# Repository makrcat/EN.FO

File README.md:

## outdoorsy-gadget

The **EN.FO** is a personal project for tracking the environment when outdoors. It measures altitude (pressure), temperature, humidity, and air quality through the BME680 chip. And it also has games now :3c

Around the end stages submitted to hack club stardance.

## Why I made this

I found a BME680 in a store, and I'd seen people making these home weather station setups and using temperature sensors for their first projects. I thought it would be cool to be able to track the weather while outside too, like while hiking or going somewhere without wifi! 

It would be pretty neat to get momentary values from a sensor for the surrounding area instead of looking online.

## CAD models

https://cad.onshape.com/documents/2de4779b51845175f3a3e786/w/7837df9d32ef23797361ec83/e/9a8511381228d62ac6592067?renderMode=0&uiState=6abf75e68beab4dd691114fb 

## Flashing to ESP32

**Materials:** 
- You want an esp32 with at least 512kb of RAM, or else it can't run the heavy graphics of circuitpython.
- You need a similar ST7789-driven screen, a microcontroller as specified above, and a bme680.
- Also, having a fuse would probably be good (just in case you short out components).

Install circuitpython! Then,

I use vscode to program, but I used Thonny to handle the flashing.
- Programs that go into the microcontroller are  `src`, `graphics`, `settings.json`, `logger.json`, and `fontsPCF`, side by side on root`/`. 
- You also have to install the libraries separately on Thonny, but it only takes a bit.

## In case you want to actually make one

Check if you are soldering the ESP-32 so that it's "bottom side up", or label-side up. The USB-C should be on the bottom. Same goes with the UPS module, make sure the USB-C is on the bottom. Or else you have to edit the CAD to match.

## Testing the program locally

I wanted to test the UI quickly, so the computer simulation is for that. The data is simulated in `mockIC.py`. 

`⚠️` Important note!! Open the `firmware` folder by itself! Otherwise, vscode will read the file paths incorrectly.

## Other images

This project originally started with a BMP & an e-ink, but gradually didn't work for the use case. I have a cool e-ink now, though.

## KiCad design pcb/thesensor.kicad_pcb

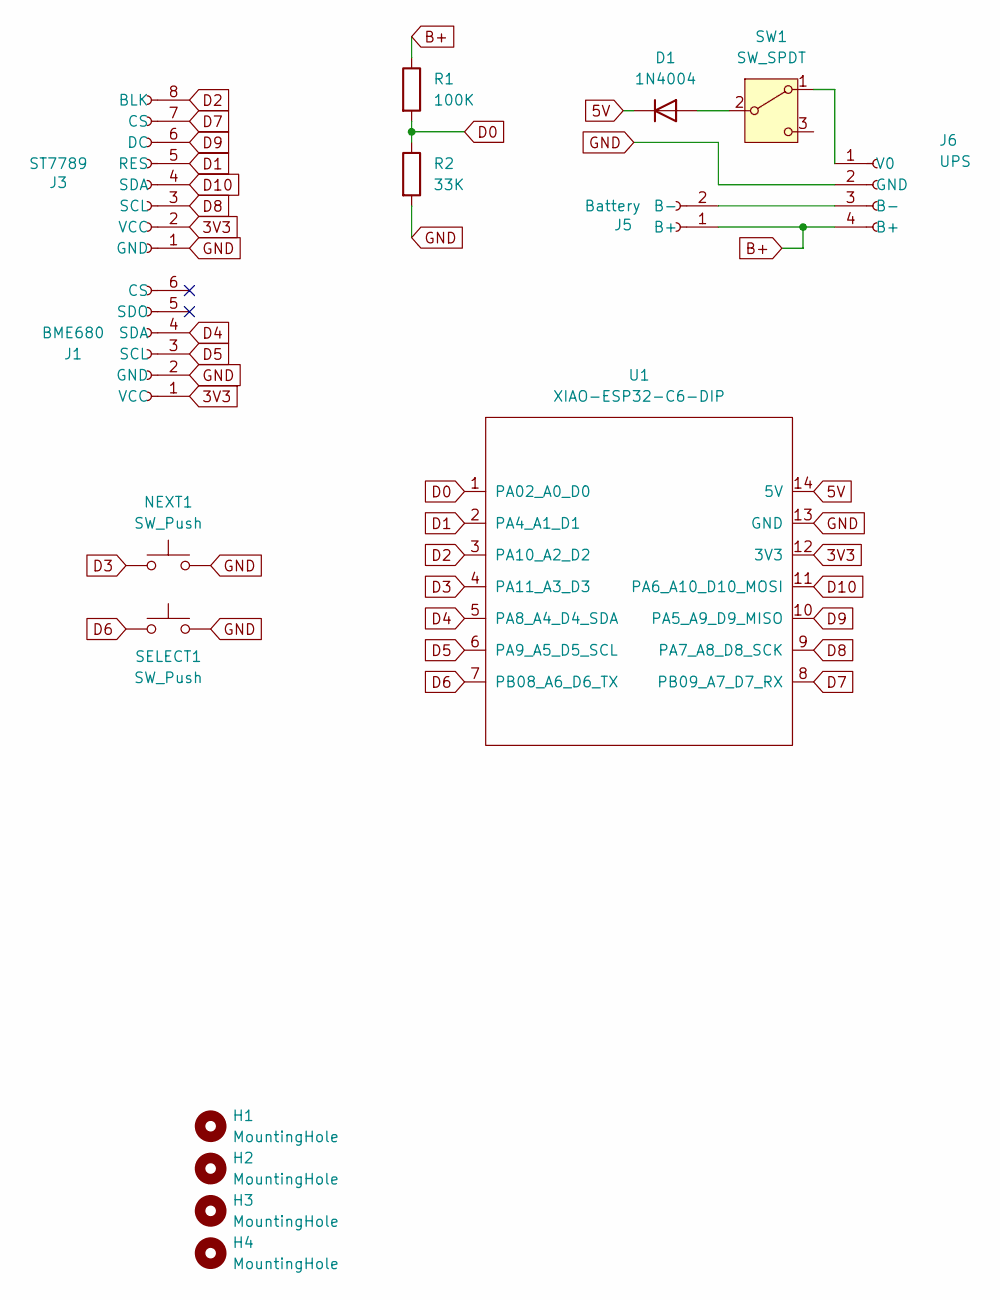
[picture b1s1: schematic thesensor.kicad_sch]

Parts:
D1: 1N4004; D_DO-41_SOD81_P10.16mm_Horizontal
H1, H2, H3, H4: MountingHole; MountingHole_2.2mm_M2_Pad
J1: BME680; PinSocket_1x06_P2.54mm_Vertical
J3: ST7789; PinSocket_1x08_P2.54mm_Vertical
J5: Battery; JST_PH_S2B-PH-K_1x02_P2.00mm_Horizontal
J6: UPS; PinSocket_1x04_P2.54mm_Vertical
NEXT1: SW_Push; SW_PUSH_6mm
R1: 100K; R_Axial_DIN0207_L6.3mm_D2.5mm_P10.16mm_Horizontal
R2: 33K; R_Axial_DIN0207_L6.3mm_D2.5mm_P10.16mm_Horizontal
SELECT1: SW_Push; SW_PUSH_6mm
SW1: SW_SPDT; SW_Slide_SPDT_Angled_CK_OS102011MA1Q
U1: XIAO-ESP32-C6-DIP

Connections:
3V3: J1.1 (VCC), J3.2 (VCC), U1.12 (3V3)
5V: D1.1 (K), U1.14 (5V)
B+: J5.1 (B+), J6.4 (B+), R1.1
D0: R1.2, R2.1, U1.1 (PA02_A0_D0)
D1: J3.5 (RES), U1.2 (PA4_A1_D1)
D2: J3.8 (BLK), U1.3 (PA10_A2_D2)
D3: NEXT1.1, U1.4 (PA11_A3_D3)
D4: J1.4 (SDA), U1.5 (PA8_A4_D4_SDA)
D5: J1.3 (SCL), U1.6 (PA9_A5_D5_SCL)
D6: SELECT1.1, U1.7 (PB08_A6_D6_TX)
D7: J3.7 (CS), U1.8 (PB09_A7_D7_RX)
D8: J3.3 (SCL), U1.9 (PA7_A8_D8_SCK)
D9: J3.6 (DC), U1.10 (PA5_A9_D9_MISO)
D10: J3.4 (SDA), U1.11 (PA6_A10_D10_MOSI)
GND: J1.2 (GND), J3.1 (GND), J6.2 (GND), NEXT1.2, R2.2, SELECT1.2, U1.13 (GND)
unnamed: D1.2 (A), SW1.2 (B)
unnamed: J5.2 (B-), J6.3 (B-)
unnamed: J6.1 (V0), SW1.1 (A)

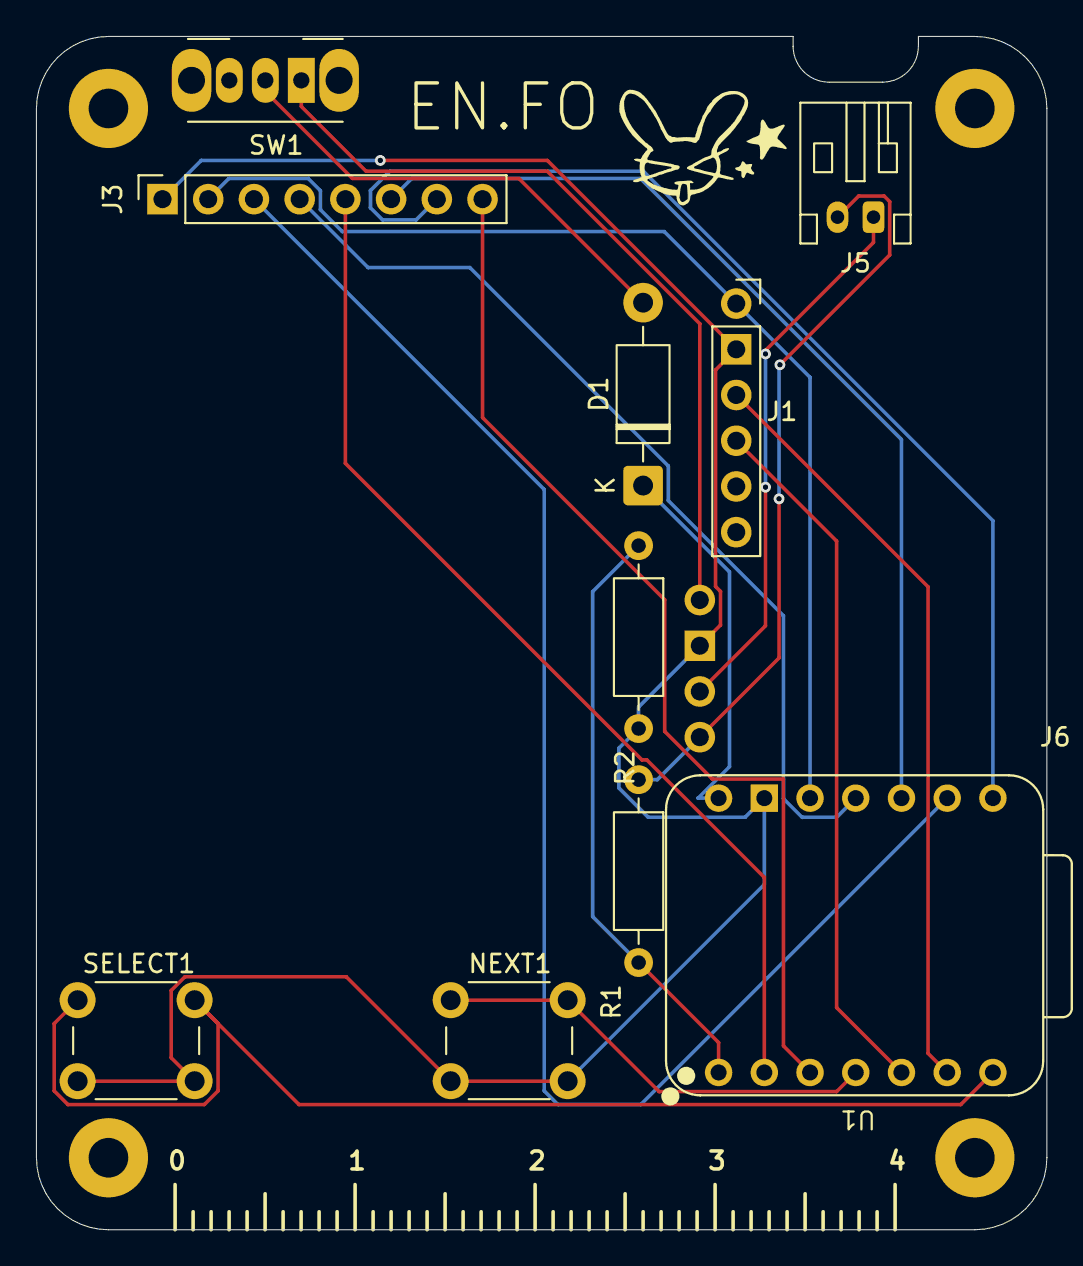
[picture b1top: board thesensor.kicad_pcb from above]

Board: 2 copper layers, 56.1 x 66.3 mm, 15 parts (0 on the bottom side), 18 nets.
